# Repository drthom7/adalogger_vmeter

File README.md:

# adalogger_vmeter
Autoranging DC voltmeter 0 to 50 volts using Feather Adalogger M0

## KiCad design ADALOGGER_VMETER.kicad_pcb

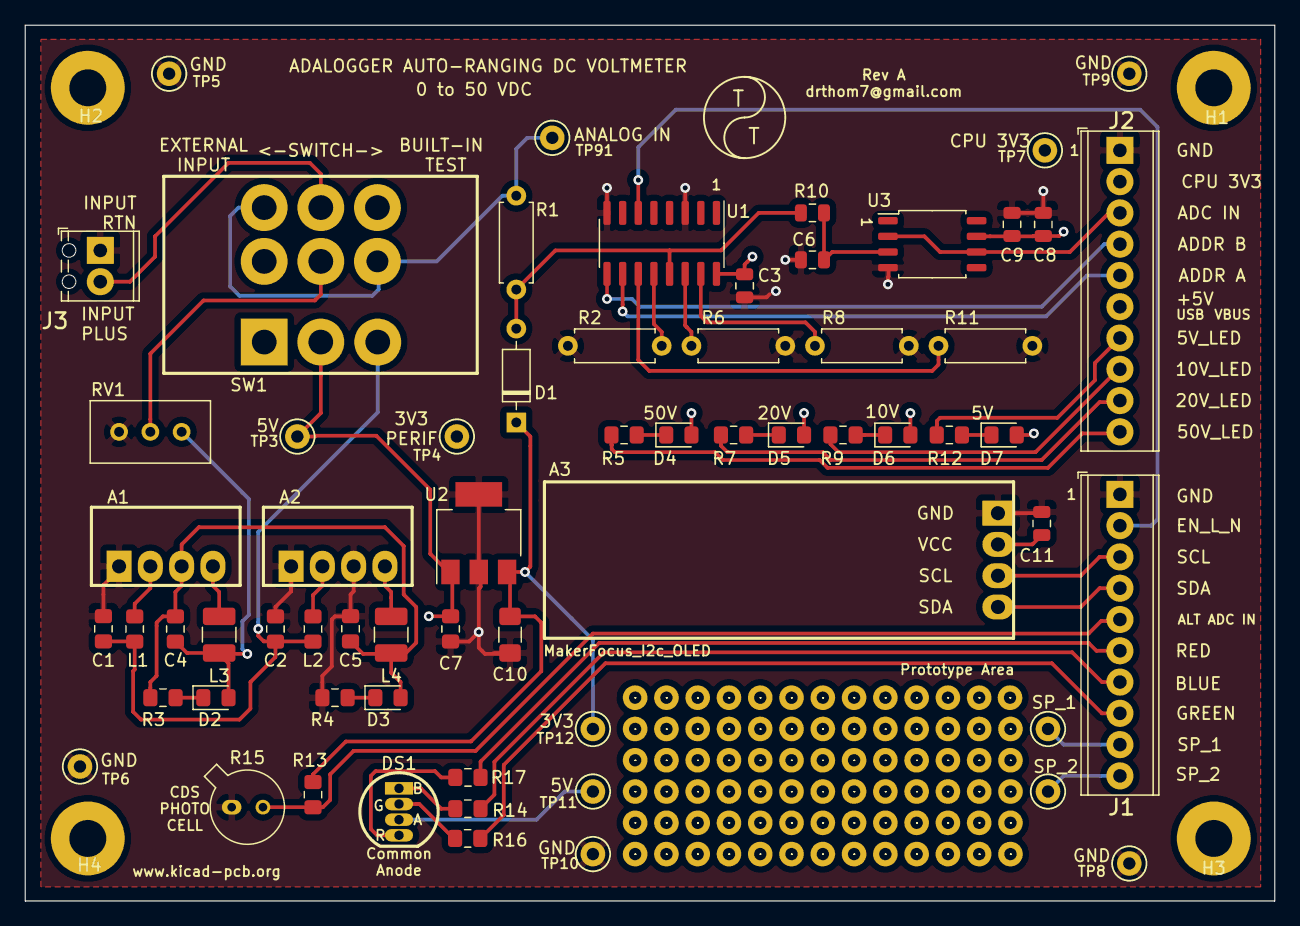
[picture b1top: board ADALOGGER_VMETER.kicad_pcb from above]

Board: 4 copper layers, 101.5 x 71.1 mm, 146 parts (0 on the bottom side), 45 nets.

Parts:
A1, A2: NME0524SC; Converter_DCDC_muRata_NMExxxxSC_THT
A3: MakerFocus_I2c_OLED
C1, C2: 4.7uF; C_0805_2012Metric_Pad1.15x1.40mm_HandSolder
C3, C9, C11: 0.1uF; C_0805_2012Metric
C4, C5, C7: 0.47uF; C_0805_2012Metric_Pad1.15x1.40mm_HandSolder
C6, C8: 1uF; C_0805_2012Metric
C10: 33uF; C_1206_3216Metric_Pad1.42x1.75mm_HandSolder
D1: bat41; D_DO-35_SOD27_P7.62mm_Horizontal
D2, D3, D4, D5, D6, D7: LED_ALT; LED_0805_2012Metric_Pad1.15x1.40mm_HandSolder
DS1: LED_BGAR; Edgelec_RGB_CA
H1, H2, H3, H4: MountingHole; MountingHole_3mm_Pad
J1, J2: Screw_Terminal_01x10; TerminalBlock_Phoenix_MPT-0,5-10-2.54_1x10_P2.54mm_Horizont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
J3: Screw_Terminal_01x02; TerminalBlock_Phoenix_MPT-0,5-2-2.54_1x02_P2.54mm_Horizontal
L1, L2: 4.7uH; L_0805_2012Metric_Pad1.15x1.40mm_HandSolder
L3, L4: 100uH; L_1210_3225Metric_Pad1.42x2.65mm_HandSolder
R1: 10 Meg; R_Axial_DIN0207_L6.3mm_D2.5mm_P7.62mm_Horizontal
R2: 750k; R_Axial_DIN0207_L6.3mm_D2.5mm_P7.62mm_Horizontal
R3, R4: 4.3k; R_0805_2012Metric_Pad1.15x1.40mm_HandSolder
R5, R7, R9, R12: 220; R_0805_2012Metric_Pad1.15x1.40mm_HandSolder
R6: 2M; R_Axial_DIN0207_L6.3mm_D2.5mm_P7.62mm_Horizontal
R8: 4.99M; R_Axial_DIN0207_L6.3mm_D2.5mm_P7.62mm_Horizontal
R10: 10K; R_0805_2012Metric
R11: 20M; R_Axial_DIN0207_L6.3mm_D2.5mm_P7.62mm_Horizontal
R13: 10k; R_0805_2012Metric_Pad1.15x1.40mm_HandSolder
R14: 442; R_0805_2012Metric_Pad1.15x1.40mm_HandSolder
R15: CDS PhotoCell; TO-18-2_Lens
R16: 475; R_0805_2012Metric_Pad1.15x1.40mm_HandSolder
R17: 604; R_0805_2012Metric_Pad1.15x1.40mm_HandSolder
RV1: 100k; Potentiometer_Bourns_3296W_Vertical
SW1: SW_3PDT; GF-161-0005
TP1, TP2: SPARE; TestPoint_Keystone_5000-5004_Miniature
TP3, TP11: 5V; TestPoint_Keystone_5000-5004_Miniature
TP4, TP12: 3V3 PERIF; TestPoint_Keystone_5000-5004_Miniature
TP5, TP6, TP8, TP9, TP10: GND; TestPoint_Keystone_5000-5004_Miniature
TP7: CPU 3V3; TestPoint_Keystone_5000-5004_Miniature
TP13, TP14, TP15, TP16, TP17, TP18, TP19, TP20, TP21, TP22, TP23, TP24, TP25, TP26, TP27, TP28, TP29, TP30, TP31, TP32, TP33, TP34, TP35, TP36, TP37, TP38, TP39, TP40, TP41, TP42, TP43, TP44, TP45, TP46, TP47, TP48, TP49, TP50, TP51, TP52, TP53, TP54, TP55, TP56, TP57, TP58, TP59, TP60, TP61, TP62, TP63, TP64, TP65, TP66, TP67, TP68, TP69, TP70, TP71, TP72, TP73, TP74, TP75, TP76, TP77, TP78, TP79, TP80, TP81, TP82, TP83, TP84, TP85, TP86, TP87, TP88, TP89, TP90: nc; TestPoint_Loop_D1.80mm_Drill1.0mm_Beaded
TP91: ANALOG IN; TestPoint_Keystone_5000-5004_Miniature
U1: MAX4618CSE+; SOIC-16_3.9x9.9mm_P1.27mm
U2: LM3940IMP-3.3; SOT-223
U3: MCP6241-E/P; SOIC-8_5.23x5.23mm_P1.27mm

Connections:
+3.3VP: A3.2, C10.1, C11.2, D1.1, R13.2, TP4.1, TP12.1, U2.3
+3V3: C3.1, C8.1, C9.1, J2.2, TP7.1, U1.16, U3.7
+5V: C7.1, D4.2, D5.2, D6.2, D7.2, DS1.3, J2.6, SW1.2, TP3.1, TP11.1, U2.1
+48V: C4.1, D2.2, L3.2, RV1.1
/5V_LED: J2.7, R12.1
/5V_SW: C1.1, C2.1, L1.1, L2.1, SW1.3
/10V_LED: J2.8, R9.1
/20V_LED: J2.9, R7.1
/50V_LED: J2.10, R5.1
/ADDR_A: J2.5, U1.10
/ADDR_B: J2.4, U1.9
/ALT_ADC_IN: J1.5, R13.1, R15.2
/BLUE: J1.7, R14.1
/EN_L_N: J1.2, U1.6
/GRN: J1.8, R16.1
/INPUT_PLUS: J3.2, SW1.8
/RED: J1.6, R17.1
/SCL: A3.3, J1.3
/SDA: A3.4, J1.4
/SP_1: J1.9, TP1.1
/SP_2: J1.10, TP2.1
/TO_ADC_IN: J2.3, U3.2, U3.6
GND: A1.1, A2.1, A2.3, A3.1, C1.2, C2.2, C3.2, C5.2, C6.2, C7.2, C8.2, C9.2, C10.2, C11.1, J1.1, J2.1, J3.1, R2.1, R4.1, R6.1, R8.1, R11.1, R15.1, RV1.3, TP5.1, TP6.1, TP8.1, TP9.1, TP10.1, U1.3, U1.8, U2.2, U2.4, U3.4
unnamed: A1.2, L1.2
unnamed: A1.3, C4.2, C5.1, D3.2, L4.2, R3.1
unnamed: A1.4, L3.1
unnamed: A2.2, L2.2
unnamed: A2.4, L4.1
unnamed: C6.1, R10.1, U3.3
unnamed: D1.2, R1.1, R10.2, U1.13
unnamed: D2.1, R3.2
unnamed: D3.1, R4.2
unnamed: D4.1, R5.2
unnamed: D5.1, R7.2
unnamed: D6.1, R9.2
unnamed: D7.1, R12.2
unnamed: DS1.1, R14.2
unnamed: DS1.2, R16.2
unnamed: DS1.4, R17.2
unnamed: R1.2, SW1.6, SW1.7, TP91.1
unnamed: R2.2, U1.12
unnamed: R6.2, U1.14
unnamed: R8.2, U1.15
unnamed: R11.2, U1.11
unnamed: RV1.2, SW1.5
